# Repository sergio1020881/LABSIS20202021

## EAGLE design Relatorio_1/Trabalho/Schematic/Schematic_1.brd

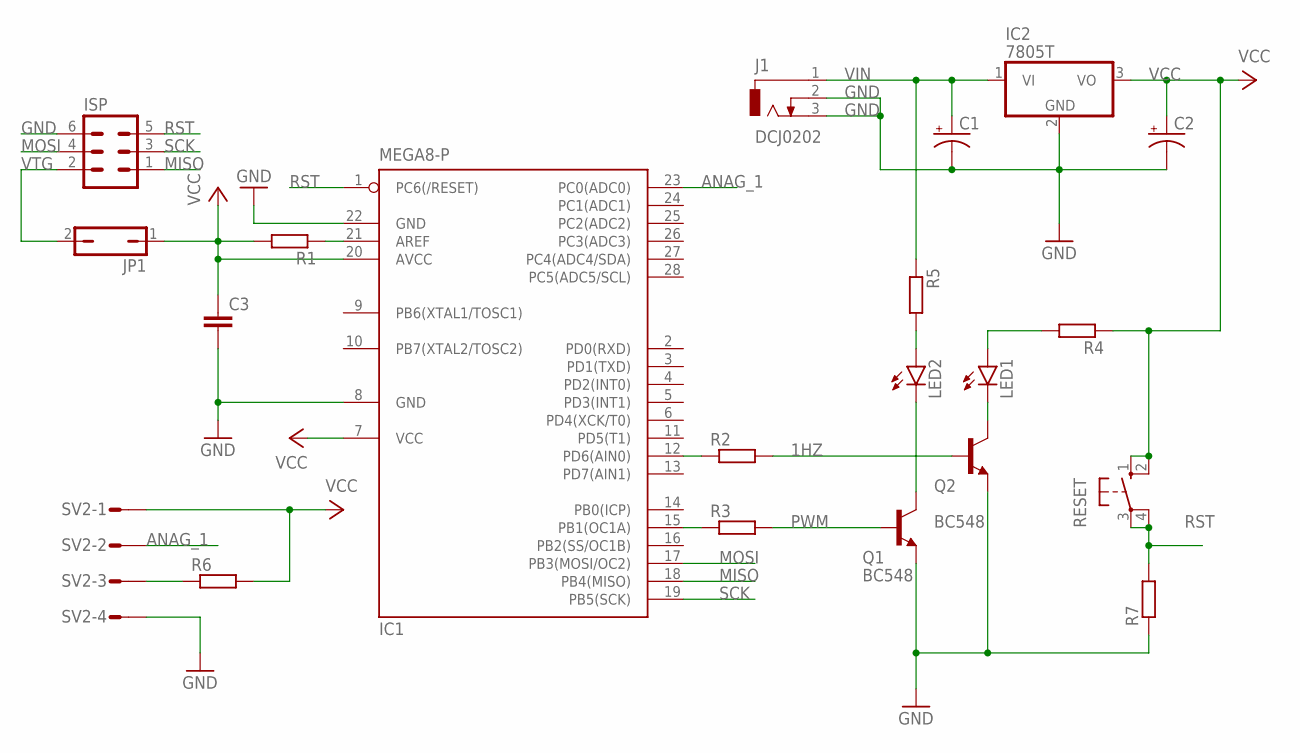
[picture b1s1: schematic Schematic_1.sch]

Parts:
C1, C2: CPOL-USE2.5-7; E2,5-7
C3: C-EU025-025X050; C025-025X050
IC1: MEGA8-P; DIL28-3
IC2: 7805T; TO220H
ISP: ML6
J1: DCJ0202
JP1: JP1Q; JP1
LED1, LED2: LEDB156; Q62902-B156
Q1, Q2: BC548; TO92-EBC
R1, R2, R3, R4, R5, R6, R7: R-EU_0207/7; 0207/7
RESET: 10-XX; B3F-10XX
SV2: L04P

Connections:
1HZ: Q2.B, R2.2
ANAG_1: IC1.23 (PC0(ADC0)), SV2.2
GND: C1.-, C2.-, C3.2, IC1.8 (GND), IC1.22 (GND), IC2.2 (GND), ISP.6, J1.2, J1.3, Q1.E, Q2.E, R7.1, SV2.4
MISO: IC1.18 (PB4(MISO)), ISP.1
MOSI: IC1.17 (PB3(MOSI/OC2)), ISP.4
unnamed: IC1.21 (AREF), R1.1
unnamed: IC1.15 (PB1(OC1A)), R3.1
unnamed: IC1.12 (PD6(AIN0)), R2.1
unnamed: R6.1, SV2.3
unnamed: LED2.K (C), Q1.C
unnamed: LED2.A, R5.2
unnamed: LED1.A, R4.2
unnamed: LED1.K (C), Q2.C
PWM: Q1.B, R3.2
RST: IC1.1 (PC6(/RESET)), ISP.5, R7.2, RESET.3, RESET.4 (P1)
SCK: IC1.19 (PB5(SCK)), ISP.3
VCC: C2.+, C3.1, IC1.7 (VCC), IC1.20 (AVCC), IC2.3 (VO), JP1.1, R1.2, R4.1, R6.2, RESET.1 (S), RESET.2 (S1), SV2.1
VIN: C1.+, IC2.1 (VI), J1.1, R5.1
VTG: ISP.2, JP1.2

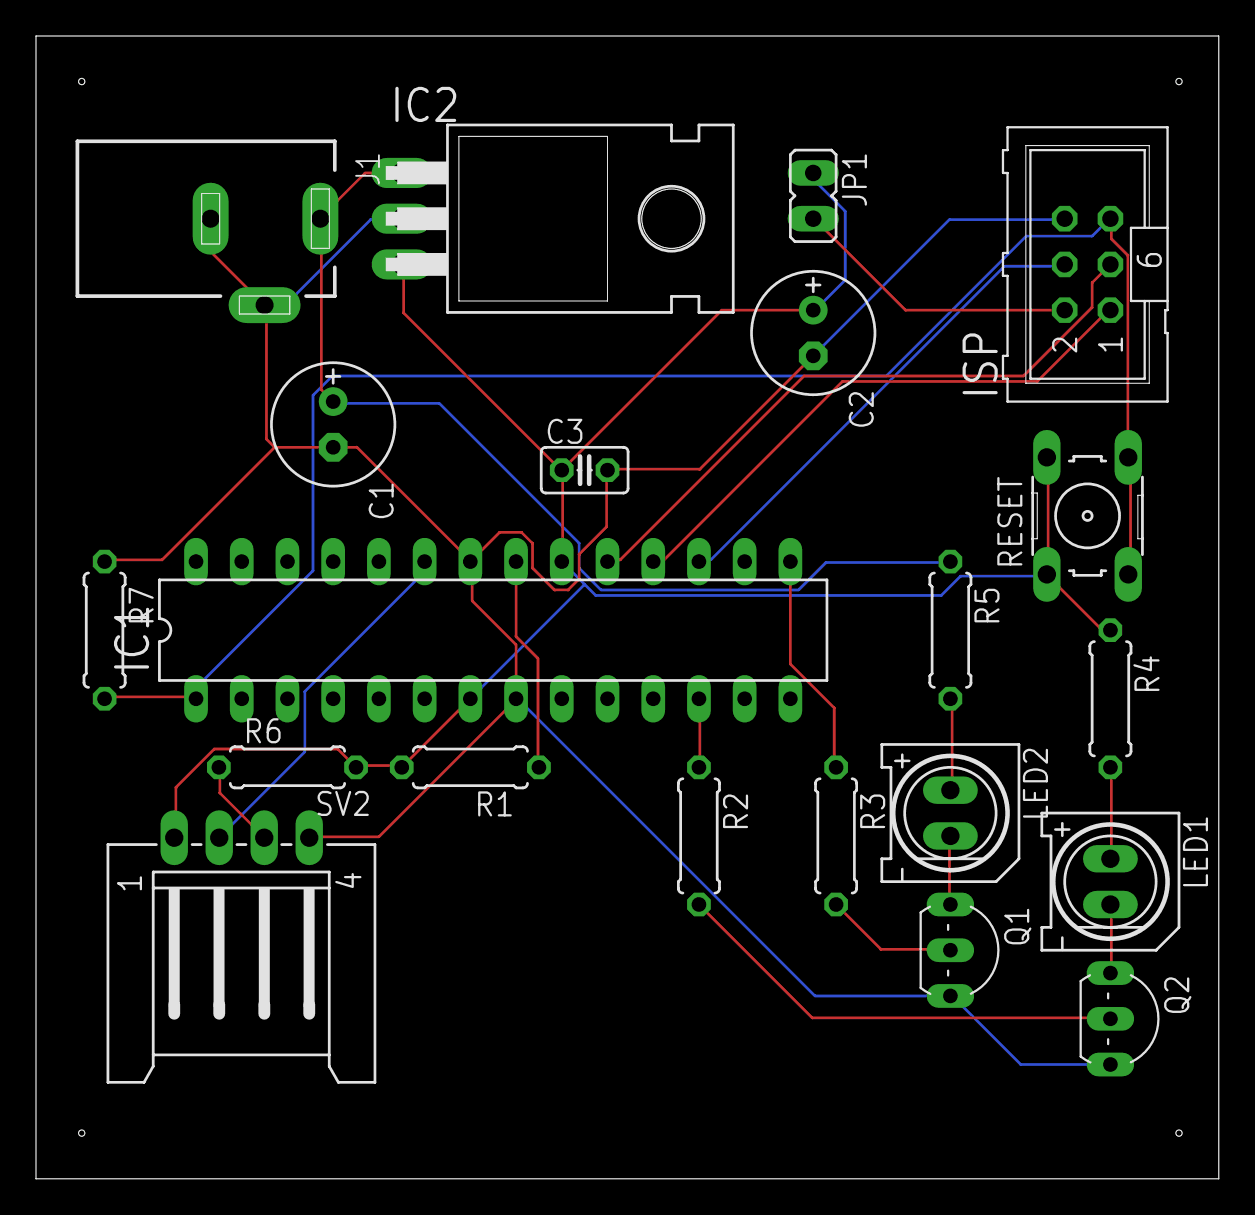
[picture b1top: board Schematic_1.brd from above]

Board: 2 copper layers, 65.7 x 63.5 mm, 21 parts (0 on the bottom side), 19 nets.

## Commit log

2020-10-07 relatorio_antigo
2020-10-08 simulacaoasmc
2020-10-08 labsis74h595
2020-10-08 labsis74h595testingphase
2020-10-08 relatorios_fix
2020-10-08 74HC595_test_1
2020-10-08 74HC595_test_2
2020-10-08 relatorio_fix_1
2020-10-08 relatorio_fix_2_nomesdocentes
2020-10-08 shift_bit
2020-10-08 shift_byte
2020-10-08 shift_data
2020-10-08 beautifullseq
2020-10-09 74hc595
2020-10-09 74hc595_1
2020-10-09 74hc595_2
2020-10-10 10102020
2020-10-12 dicionario
2020-10-12 removed
2020-10-12 org_1
2020-10-12 redo_all
2020-10-12 redo_all_1
2020-10-12 fixes_1
2020-10-13 finished_first_report
2020-10-13 finished_first_report_1
2020-10-14 start_posicao_painel
2020-10-15 schemantic
2020-10-15 org_2
2020-10-15 org_3
2020-10-15 org_4
2020-10-15 zipped_1
2020-10-15 org_5
2020-10-15 folder
2020-10-15 folder_1
2020-10-17 notes
2020-10-17 sequence
2020-10-18 restart_proj_suntrack
2020-10-19 code_a_bit
2020-10-20 keypad_upgrade
2020-10-20 keypad_testdrive
2020-10-20 keypad_upgrade_2
2020-10-20 manualandsensormenu
2020-10-20 starti2cclocksetup
2020-10-20 relatoriotemplate
2020-10-20 added_RTC
2020-10-20 Magic
2020-10-20 Nearly_finished
2020-10-20 BCKP_update
2020-10-21 cleanup_syntax
2020-10-21 fix_bugs
2020-10-21 addon
2020-10-21 upgrade
2020-10-21 removebckp
2020-10-21 research
2020-10-21 syntax
2020-10-22 uart1_ftdi_pc_putty
2020-10-22 tx_position_tx_time
2020-10-22 finished_project_just_small_fixes_now
2020-10-22 fix_uart_transmit
2020-10-22 fix_uart_rxflush
2020-10-23 schoolorg
2020-10-24 uart_more_fixes
2020-10-24 uart_fine_tunning
2020-10-24 note
2020-10-24 setupuartandtimer
2020-10-25 semantics
2020-10-25 semantics_1
2020-10-25 semantics_4
2020-10-25 semantics_5
2020-10-25 semantics_10
2020-10-31 cleanup
2020-10-31 sense
2020-11-02 estadoarte_1
2020-11-06 Estado_de_Arte_Start
2020-11-07 estado_1
2020-11-07 estado_2
2020-11-07 estado_3
2020-11-08 estado_arte_1
2020-11-09 estado_arte_2
2020-11-09 estado_arte_3
2020-11-11 estado_arte_4
2020-11-15 update15112020
2020-11-15 notas
2020-11-26 htmltrial
2020-11-26 htmlprep
2020-11-27 htmlprep_1
2020-11-27 htmlprep_2
2020-11-27 htmlprep_3
2020-11-27 htmlsyntaxmodel
2020-11-27 htmlsyntaxmodel_1
2020-11-27 htmlexplorecode
2020-11-27 htmlbeginrel
2020-11-28 htmlbeginrel_1
2020-11-28 htmlbeginrel_2
2020-11-28 htmlbeginrel_3
2020-11-28 htmlfix
2020-11-29 fluxograma
2020-11-29 SYNTAX_1
2020-11-29 SYNTAX_2
2020-11-29 bibliography_1
2020-11-29 flowchart_new
2020-11-29 datasheets
2020-11-30 30112020
2020-11-30 code structure
2020-11-30 scratch_1
2020-12-01 scratch__2
2020-12-01 nearly finished
2020-12-02 hard sh
2020-12-02 hard_1
2020-12-02 pacience
2020-12-02 nearly there wait
2020-12-02 nearly there wait_1
2020-12-02 schematics
2020-12-02 falta simulação e videos_resultados
2020-12-02 videos_resultados
2020-12-02 videos
2020-12-03 wait
2020-12-03 plan_1
2020-12-03 labsis
2020-12-04 manuais
2020-12-04 cleanup_2
2020-12-05 cleanup_3
2020-12-05 cleanup_4
2020-12-05 cleanup_5
2020-12-05 finished
2020-12-05 finished_all
2020-12-06 finished_all_1
2020-12-06 finished_all_2
2020-12-06 presentation
2020-12-08 07122020
2020-12-08 07122020_1
2020-12-08 08122020
2020-12-09 08122020_2
2020-12-19 19122020_1
2020-12-20 20122020_1
2021-01-14 14012021
2021-01-19 19012021
2021-01-19 refresh
2021-01-21 21012021
2021-01-25 messages
2021-01-27 plan
2021-01-28 remove
2021-01-29 eval_2
2021-02-01 linkbotnrol
2021-02-10 Nota_Final
2021-02-11 result
2021-02-11 result_1
2021-02-11 calc
2021-02-11 result_3
2021-02-12 myfirstlcdlib
2021-02-12 mylcdlib
2021-02-14 definicao
2021-02-15 exponencial
2021-02-15 exponencial_1
2021-02-16 notas_labsis_12020221
2021-02-18 evaluation
2021-02-19 ampop
2021-02-26 labsis_1
2021-03-15 fix_bug_LCD
2021-03-16 review_see_if_all_still_OK
2021-03-19 update_func_lib
2021-03-25 remove_libs
2021-06-21 2021
2021-07-11 finished-1
